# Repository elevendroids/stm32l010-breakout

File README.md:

# STM32L010 Breakout Board (Rev. B)

Small MCU board designed primarly for the STM32L010K8T6 ARM Cortex-M0+ microcontroller: [Datasheet](https://www.st.com/resource/en/datasheet/stm32l010k8.pdf)

Can also be used with other pin-compatible STM32 MCUs in LQFP-32 package:
- Most of the STM32L0 family
- STM32L4x2 (ARM Cortex-M4)

## Features

- minimal subset of components, no power regulation (important when playing with low power apps)
- optional LSE crystal, if not used its GPIO pins can be connected to the user header by soldering relevant 0R resistors (see schematic)
- two buffered user LEDs, connected to the header - no reserved GPIOs
- reset button
- standard 0.05" pitch SWD programming header, SWD signals also present on the pin headers

Designed in KiCad 5.1.6

Schematic: [PDF](docs/stm32l010-breakout.pdf)

License: [CC BY-SA 4.0](https://creativecommons.org/licenses/by-sa/4.0/)

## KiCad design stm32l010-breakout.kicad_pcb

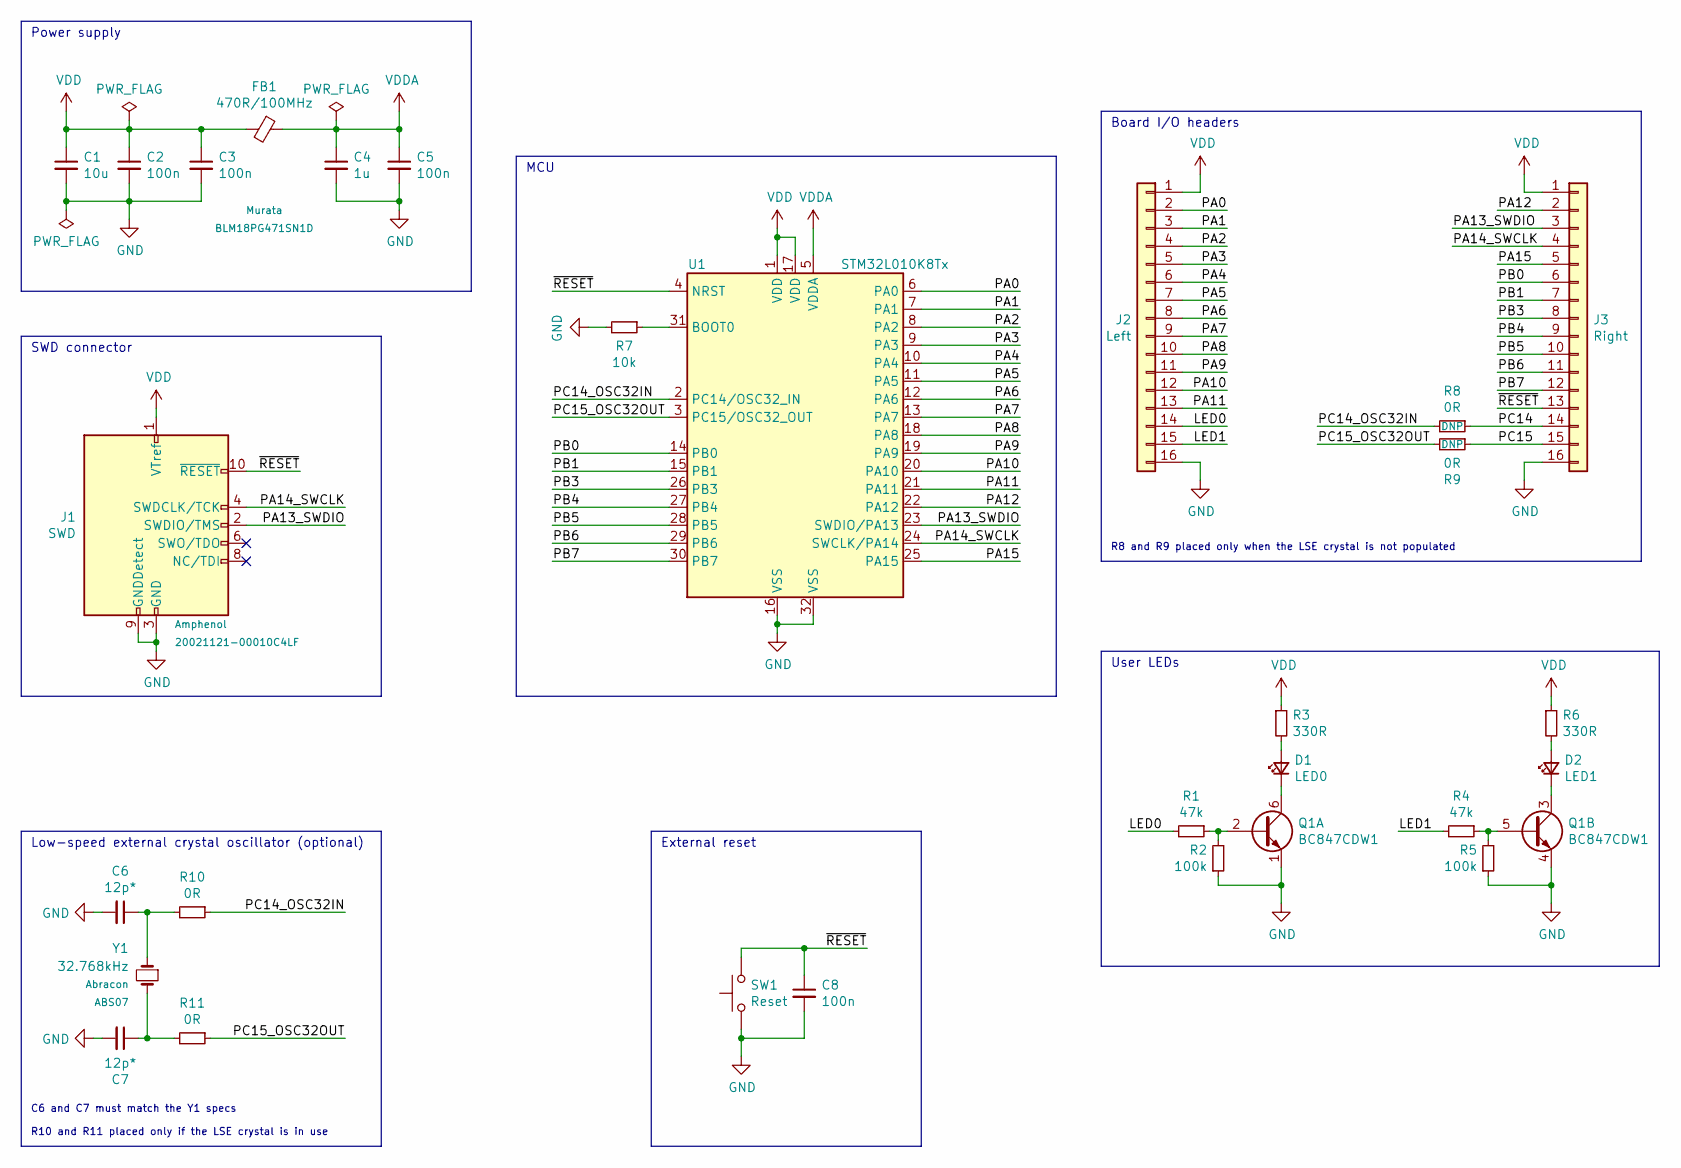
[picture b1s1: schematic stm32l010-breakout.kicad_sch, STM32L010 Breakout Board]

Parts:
C1: 10u; C_0805_2012Metric
C2, C3, C5, C8: 100n; C_0603_1608Metric
C4: 1u; C_0603_1608Metric
C6, C7: 12p*; C_0603_1608Metric
D1: LED0; LED_0805_2012Metric
D2: LED1; LED_0805_2012Metric
FB1: 470R/100MHz; L_0603_1608Metric; MPN BLM18PG471SN1D
J1: SWD; PinHeader_2x05_P1.27mm_Vertical_SMD; MPN 20021121-00010C4LF
J2: Left; PinHeader_1x16_P2.54mm_Vertical
J3: Right; PinHeader_1x16_P2.54mm_Vertical
Q1: BC847CDW1; SOT-363_SC-70-6
R1, R4: 47k; R_0603_1608Metric
R2, R5: 100k; R_0603_1608Metric
R3, R6: 330R; R_0603_1608Metric
R7: 10k; R_0603_1608Metric
R8, R9, R10, R11: 0R; R_0603_1608Metric
SW1: Reset; SW_SPST_CK_RS282G05A3
U1: STM32L010K8Tx; LQFP-32_7x7mm_P0.8mm; MPN STM32L010K8T6
Y1: 32.768kHz; Crystal_SMD_3215-2Pin_3.2x1.5mm; MPN ABS07

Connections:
/LED0: J2.14, R1.2
/LED1: J2.15, R4.2
/PA0: J2.2, U1.6 (PA0)
/PA1: J2.3, U1.7 (PA1)
/PA2: J2.4, U1.8 (PA2)
/PA3: J2.5, U1.9 (PA3)
/PA4: J2.6, U1.10 (PA4)
/PA5: J2.7, U1.11 (PA5)
/PA6: J2.8, U1.12 (PA6)
/PA7: J2.9, U1.13 (PA7)
/PA8: J2.10, U1.18 (PA8)
/PA9: J2.11, U1.19 (PA9)
/PA10: J2.12, U1.20 (PA10)
/PA11: J2.13, U1.21 (PA11)
/PA12: J3.2, U1.22 (PA12)
/PA13_SWDIO: J1.2 (SWDIO/TMS), J3.3, U1.23 (SWDIO/PA13)
/PA14_SWCLK: J1.4 (SWDCLK/TCK), J3.4, U1.24 (SWCLK/PA14)
/PA15: J3.5, U1.25 (PA15)
/PB0: J3.6, U1.14 (PB0)
/PB1: J3.7, U1.15 (PB1)
/PB3: J3.8, U1.26 (PB3)
/PB4: J3.9, U1.27 (PB4)
/PB5: J3.10, U1.28 (PB5)
/PB6: J3.11, U1.29 (PB6)
/PB7: J3.12, U1.30 (PB7)
/PC14: J3.14, R8.1
/PC14_OSC32IN: R8.2, R10.1, U1.2 (PC14/OSC32_IN)
/PC15: J3.15, R9.1
/PC15_OSC32OUT: R9.2, R11.1, U1.3 (PC15/OSC32_OUT)
/~RESET: C8.1, J1.10 (~RESET), J3.13, SW1.2, U1.4 (NRST)
GND: C1.2, C2.2, C3.2, C4.2, C5.2, C6.2, C7.2, C8.2, J1.3 (GND), J1.5 (GND), J1.9 (GNDDetect), J2.16, J3.16, Q1.1 (E1), Q1.4 (E2), R2.1, R5.1, R7.2, SW1.1, U1.16 (VSS), U1.32 (VSS)
unnamed: C6.1, R10.2, Y1.1
unnamed: C7.1, R11.2, Y1.2
unnamed: D1.1 (K), Q1.6 (C1)
unnamed: D1.2 (A), R3.2
unnamed: D2.1 (K), Q1.3 (C2)
unnamed: D2.2 (A), R6.2
unnamed: Q1.2 (B1), R1.1, R2.2
unnamed: Q1.5 (B2), R4.1, R5.2
unnamed: R7.1, U1.31 (BOOT0)
VDD: C1.1, C2.1, C3.1, FB1.2, J1.1 (VTref), J2.1, J3.1, R3.1, R6.1, U1.1 (VDD), U1.17 (VDD)
VDDA: C4.1, C5.1, FB1.1, U1.5 (VDDA)

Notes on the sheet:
C6 and C7 must match the Y1 specs R10 and R11 placed only if the LSE crystal is in use
Power supply
R8 and R9 placed only when the LSE crystal is not populated
SWD connector
External reset
Low-speed external crystal oscillator (optional)
MCU
Board I/O headers
User LEDs

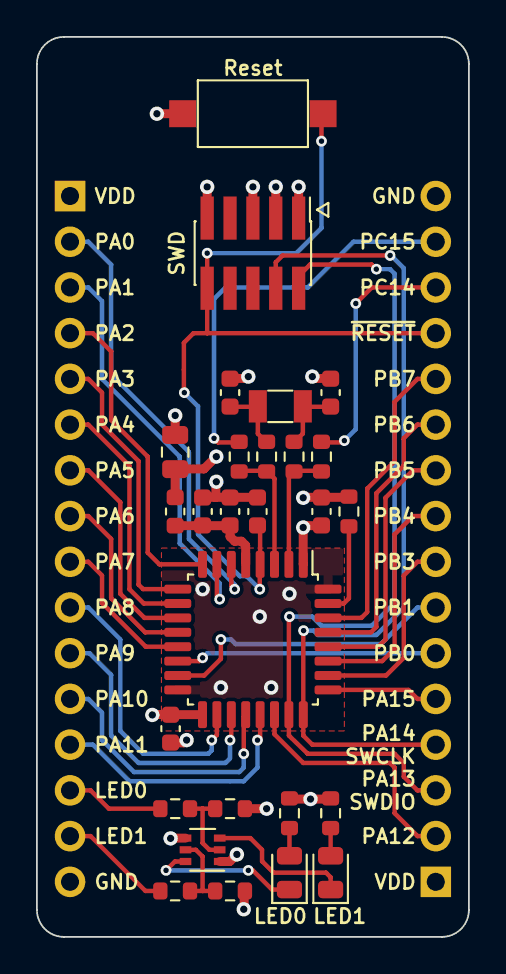
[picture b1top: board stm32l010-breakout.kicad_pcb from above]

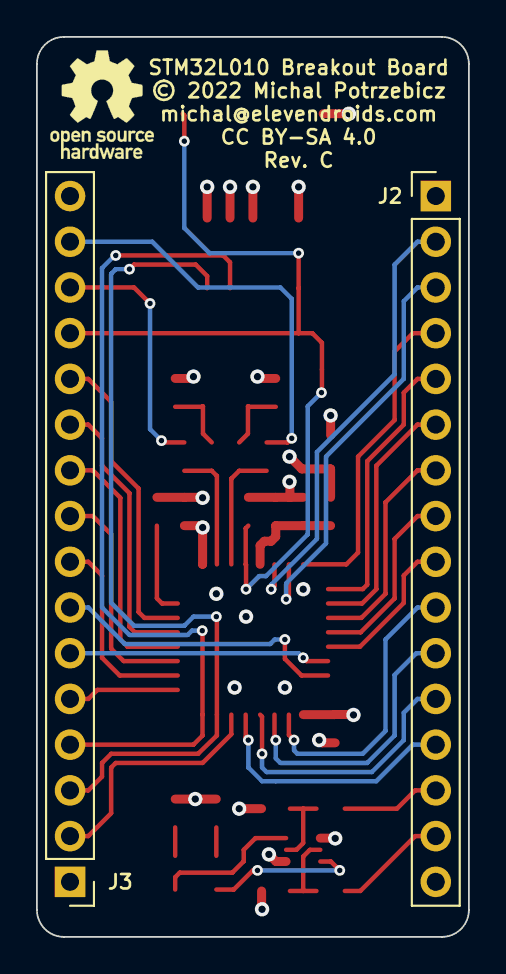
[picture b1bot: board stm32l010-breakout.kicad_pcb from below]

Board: 4 copper layers, 24.0 x 50.0 mm, 29 parts (2 on the bottom side), 42 nets.

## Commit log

2020-07-31 Initial commit
    Prototypes ordered from OSHPark
2020-08-05 Schematic cleanup, partial re-layout
    - Changed the PCB size to 25x50mm
    - Use 0R resistors for LSE oscillator/GPIO selection
    - Schematic cleanup
2020-08-05 Schematic PDF
2020-08-14 Finished laying out Revision B
2020-08-14 Updated schematic PDF
2020-08-14 Fixed copper pour settings, small tweaks
2020-08-15 Rotated the SWD connector, moved LED buffer to the front layer
2020-08-15 More PCB tweaks
2020-08-16 Finished (hopefully) layout for the Rev. B
2020-08-17 Added readme, license and a pcb render
2020-09-02 Added interactive BOM
2020-09-14 Added photo of the first OSHPark prototype
2020-09-14 README formatting
2020-09-15 Schematic cleanup
2020-11-11 Updated STM32L010 symbol
2020-11-11 Synced with library changes
2021-04-07 Schematic update due to STM32L010 library changes
2021-04-07 Updated PDF schematic
2022-04-03 Revision C with a 4 layer PCB, initial commit

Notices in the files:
stm32l010-breakout.kicad_pcb:
© 2022 Michal Potrzebicz
CC BY-SA 4.0
